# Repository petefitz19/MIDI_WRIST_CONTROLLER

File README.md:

# MIDI_WRIST_CONTROLLER
Code and Schematics for the MIDI wrist controller and its wireless attachments

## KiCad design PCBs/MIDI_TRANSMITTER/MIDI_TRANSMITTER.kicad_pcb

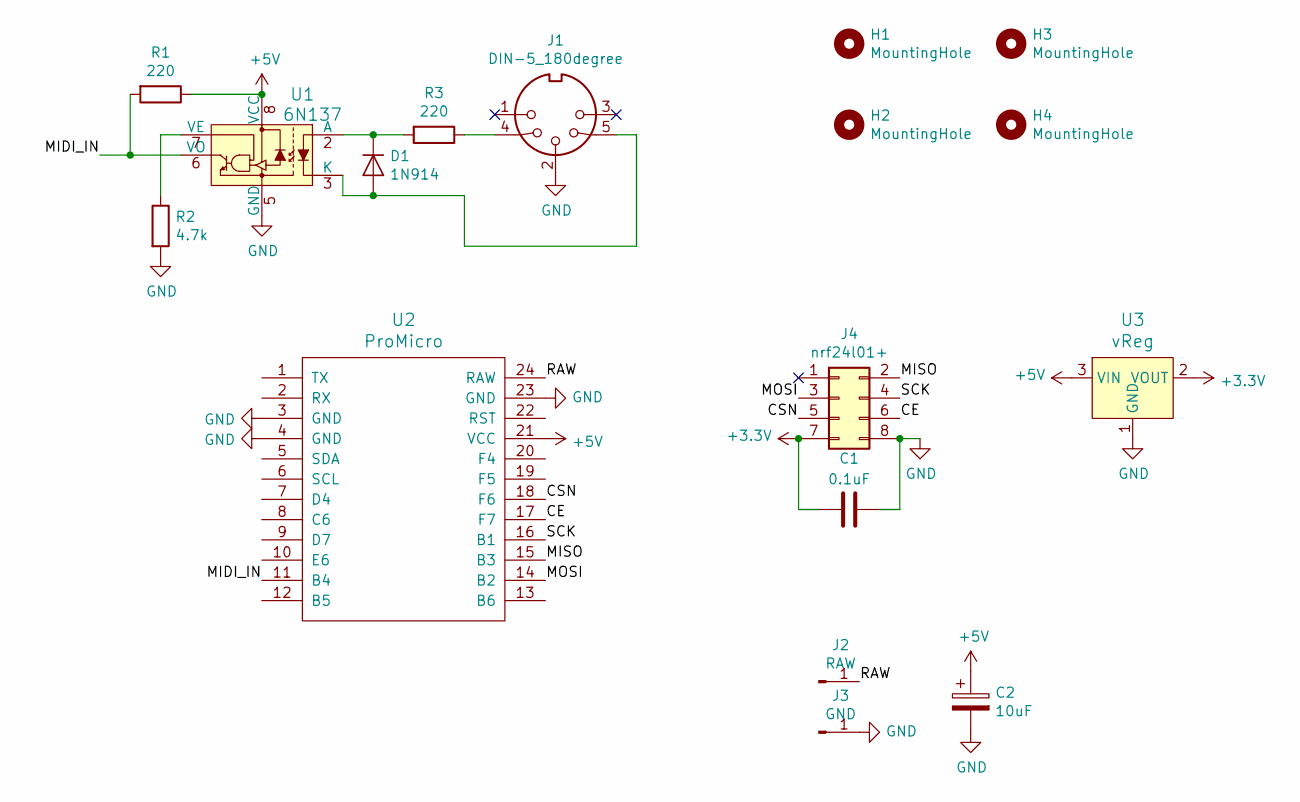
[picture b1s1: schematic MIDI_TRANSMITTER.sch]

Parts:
C1: 0.1uF; C_Disc_D3.0mm_W1.6mm_P2.50mm
C2: 10uF; CP_Radial_D4.0mm_P1.50mm
D1: 1N914; D_DO-34_SOD68_P7.62mm_Horizontal
H1, H2, H3, H4: MountingHole; MountingHole_2.2mm_M2
J1: DIN-5_180degree; Midi_jack
J2: RAW; PinSocket_1x01_P2.54mm_Vertical
J3: GND; PinSocket_1x01_P2.54mm_Vertical
J4: nrf24l01+; PinHeader_2x04_P2.54mm_Vertical
R1, R3: 220; R_Axial_DIN0207_L6.3mm_D2.5mm_P7.62mm_Horizontal
R2: 4.7k; R_Axial_DIN0207_L6.3mm_D2.5mm_P7.62mm_Horizontal
U1: 6N137; DIP-8_W7.62mm; MPN 6N137; Digi-Key_PN 160-1791-ND
U2: ProMicro
U3: vReg; TO-220-3_Vertical; MPN LD1117V33; Digi-Key_PN 497-1491-5-ND

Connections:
+3V3: C1.2, J4.7, U3.2 (VOUT)
+5V: C2.1, R1.1, U1.8 (VCC), U2.21 (VCC), U3.3 (VIN)
/CE: J4.6, U2.17 (F7)
/CSN: J4.5, U2.18 (F6)
/MIDI_IN: R1.2, U1.6 (VO), U2.11 (B4)
/MISO: J4.2, U2.15 (B3)
/MOSI: J4.3, U2.14 (B2)
/RAW: J2.1, U2.24 (RAW)
/SCK: J4.4, U2.16 (B1)
GND: C1.1, C2.2, J1.2, J3.1, J4.8, R2.2, U1.5 (GND), U2.3 (GND), U2.4 (GND), U2.23 (GND), U3.1 (GND)
unnamed: D1.1 (K), R3.2, U1.2 (A)
unnamed: D1.2 (A), J1.5, U1.3 (K)
unnamed: J1.4, R3.1
unnamed: R2.1, U1.7 (VE)

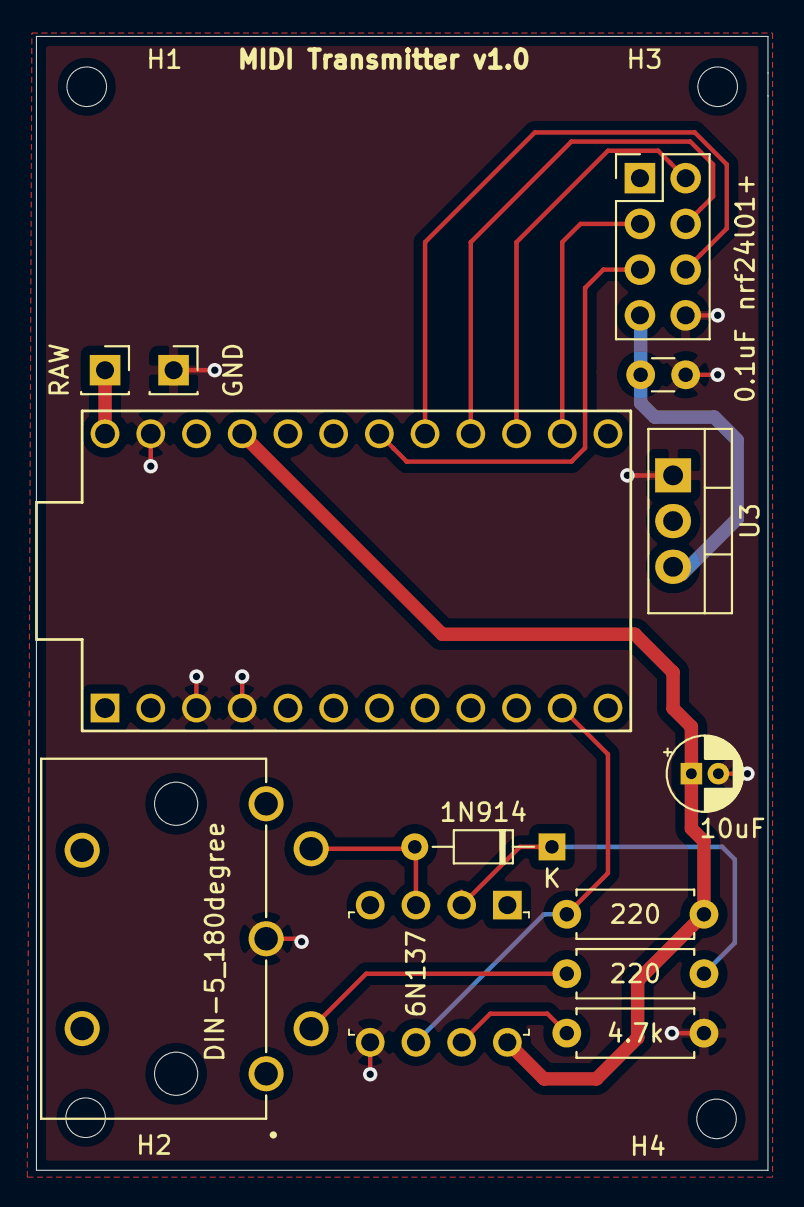
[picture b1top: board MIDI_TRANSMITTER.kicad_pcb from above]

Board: 2 copper layers, 40.6 x 63.0 mm, 17 parts (0 on the bottom side), 14 nets.

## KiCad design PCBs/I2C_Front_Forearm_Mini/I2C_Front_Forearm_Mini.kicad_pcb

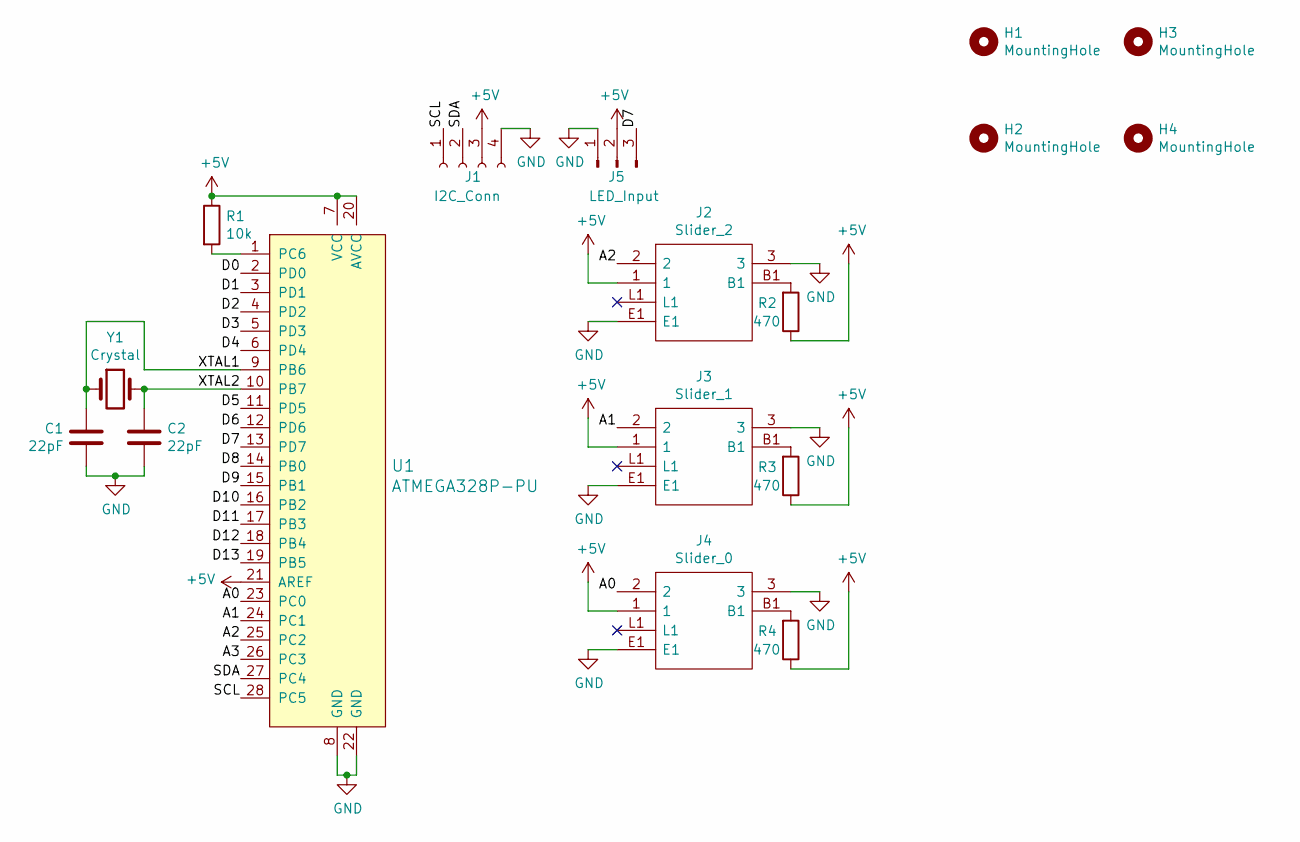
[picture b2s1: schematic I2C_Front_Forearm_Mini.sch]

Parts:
C1, C2: 22pF; C_Disc_D3.0mm_W1.6mm_P2.50mm
H1, H2, H3, H4: MountingHole; MountingHole_2mm
J1: I2C_Conn; JST_PH_B4B-PH-K_1x04_P2.00mm_Vertical
J2: Slider_2; PTL4515O1503B2; Mouser Part Number 652-PTL45-15O1-503B2
J3: Slider_1; PTL4515O1503B2; Mouser Part Number 652-PTL45-15O1-503B2
J4: Slider_0; PTL4515O1503B2; Mouser Part Number 652-PTL45-15O1-503B2
J5: LED_Input; PinHeader_1x03_P2.54mm_Vertical
R1: 10k; R_Axial_DIN0207_L6.3mm_D2.5mm_P7.62mm_Horizontal
R2, R3, R4: 470; R_Axial_DIN0207_L6.3mm_D2.5mm_P7.62mm_Horizontal
U1: ATMEGA328P-PU; DIP-28_W7.62mm; MPN ATMEGA328P-PU; Digi-Key_PN ATMEGA328P-PU-ND
Y1: Crystal; Crystal_HC52-8mm_Vertical

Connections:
+5V: J1.3, J2.1, J3.1, J4.1, J5.2, R1.1, R2.1, R3.1, R4.1, U1.7 (VCC), U1.20 (AVCC), U1.21 (AREF)
/A0: J4.2, U1.23 (PC0)
/A1: J3.2, U1.24 (PC1)
/A2: J2.2, U1.25 (PC2)
/A3: U1.26 (PC3)
/D0: U1.2 (PD0)
/D1: U1.3 (PD1)
/D2: U1.4 (PD2)
/D3: U1.5 (PD3)
/D4: U1.6 (PD4)
/D5: U1.11 (PD5)
/D6: U1.12 (PD6)
/D7: J5.3, U1.13 (PD7)
/D8: U1.14 (PB0)
/D9: U1.15 (PB1)
/D10: U1.16 (PB2)
/D11: U1.17 (PB3)
/D12: U1.18 (PB4)
/D13: U1.19 (PB5)
/SCL: J1.1, U1.28 (PC5)
/SDA: J1.2, U1.27 (PC4)
/XTAL1: C1.2, U1.9 (PB6), Y1.1
/XTAL2: C2.1, U1.10 (PB7), Y1.2
GND: C1.1, C2.2, J1.4, J2.3, J2.E1, J3.3, J3.E1, J4.3, J4.E1, J5.1, U1.8 (GND), U1.22 (GND)
unnamed: J2.B1, R2.2
unnamed: J3.B1, R3.2
unnamed: J4.B1, R4.2
unnamed: R1.2, U1.1 (PC6)

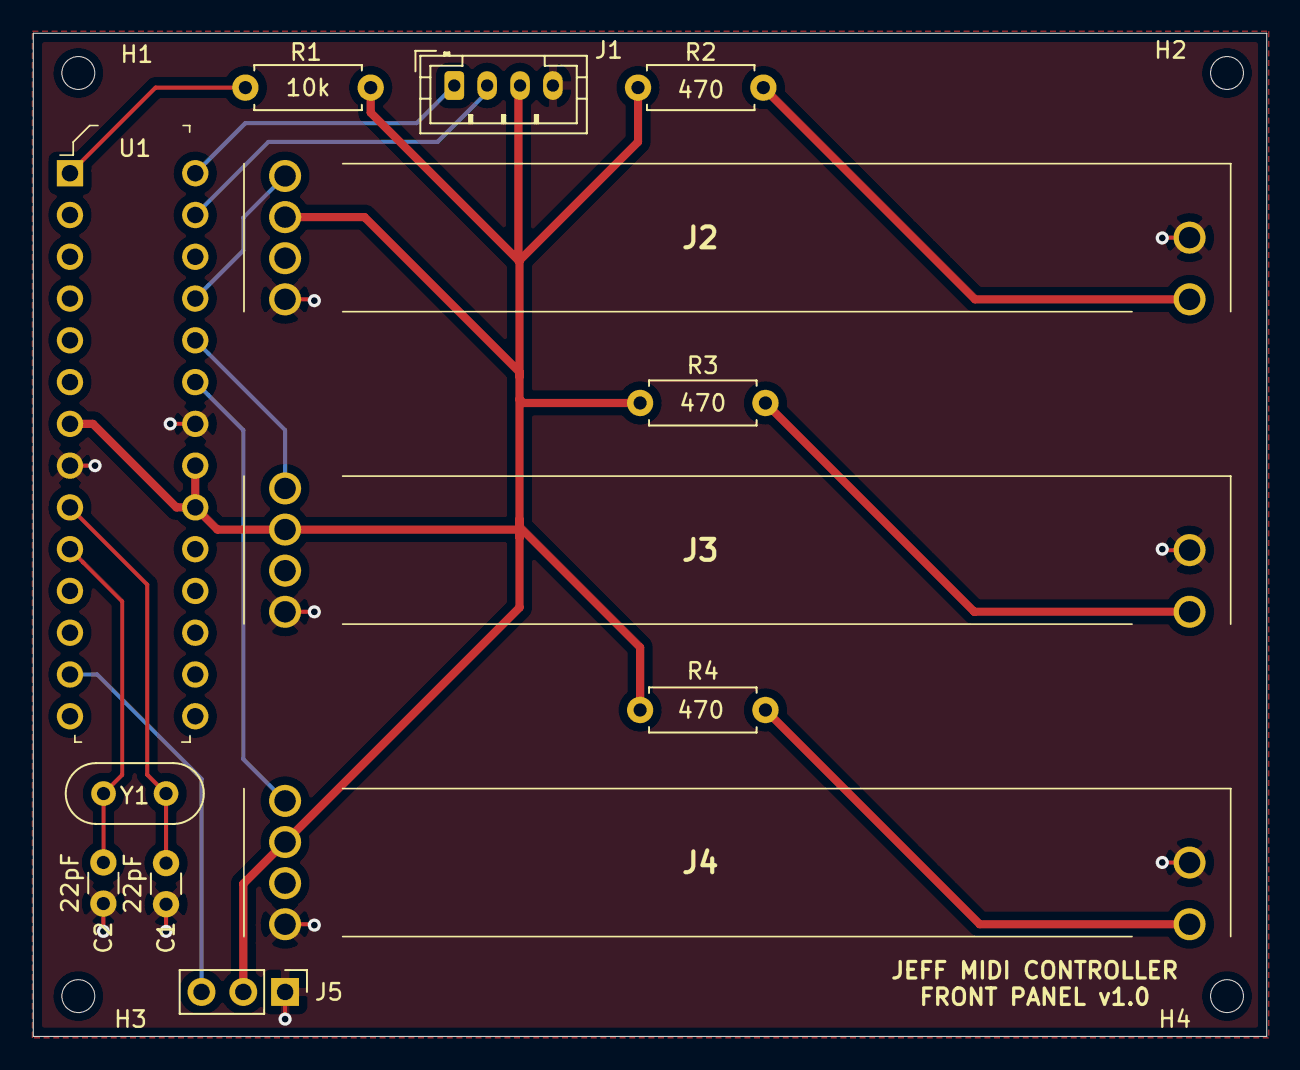
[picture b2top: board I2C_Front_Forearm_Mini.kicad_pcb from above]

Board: 2 copper layers, 75.0 x 61.0 mm, 17 parts (0 on the bottom side), 14 nets.

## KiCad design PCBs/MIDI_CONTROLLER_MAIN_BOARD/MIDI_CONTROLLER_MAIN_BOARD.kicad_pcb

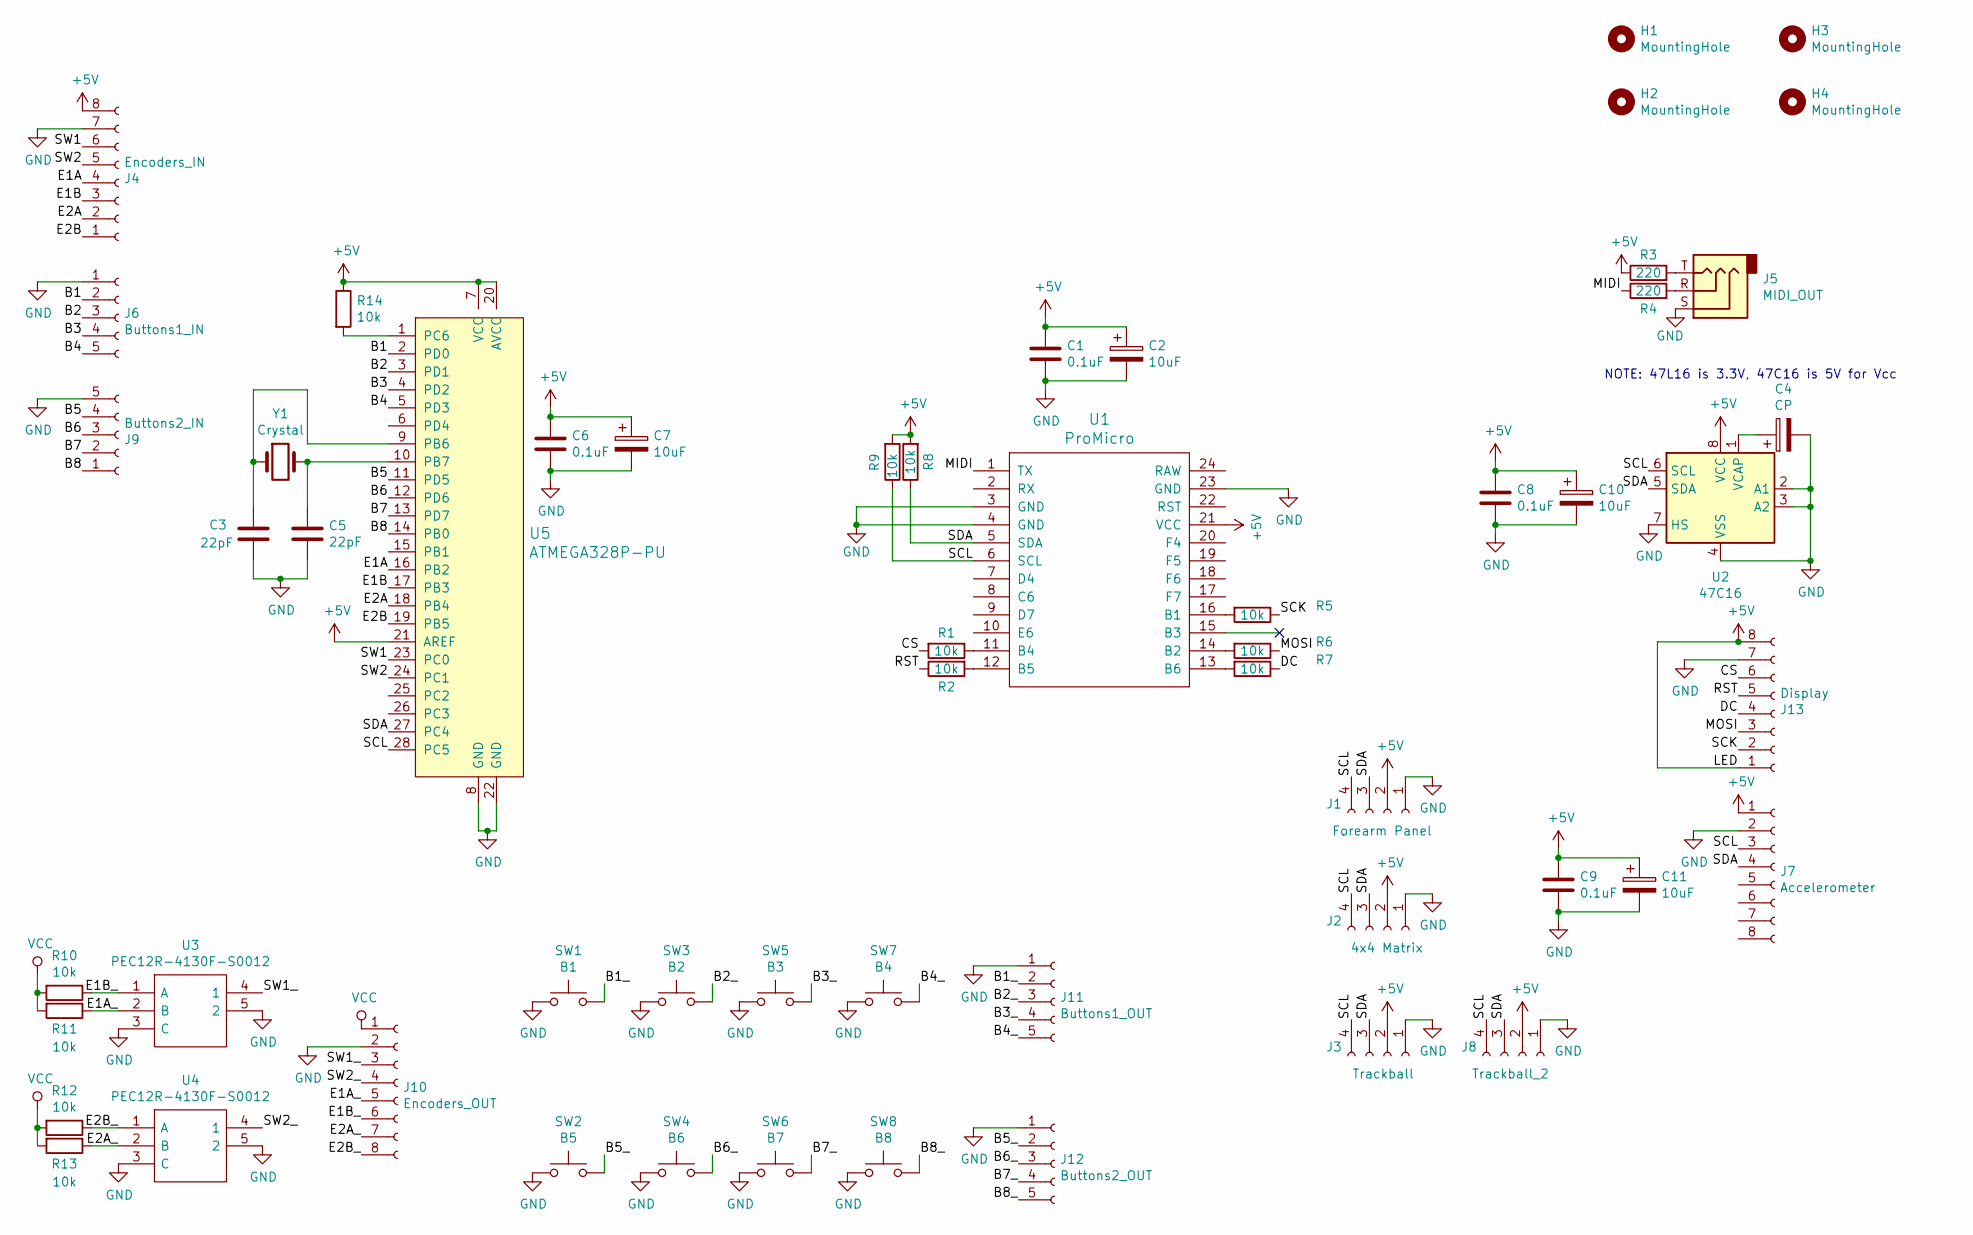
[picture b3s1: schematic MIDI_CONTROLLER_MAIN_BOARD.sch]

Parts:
C1, C6, C8, C9: 0.1uF; C_Disc_D3.0mm_W1.6mm_P2.50mm
C2, C7, C10, C11: 10uF; CP_Radial_D4.0mm_P1.50mm
C3, C5: 22pF; C_Disc_D3.0mm_W1.6mm_P2.50mm
C4: CP; CP_Radial_D4.0mm_P1.50mm
H1, H2, H3, H4: MountingHole; MountingHole_2mm
J1: Forearm Panel; JST_PH_B4B-PH-K_1x04_P2.00mm_Vertical
J2: 4x4 Matrix; JST_PH_B4B-PH-K_1x04_P2.00mm_Vertical
J3: Trackball; JST_PH_B4B-PH-K_1x04_P2.00mm_Vertical
J4: Encoders_IN; JST_XH_B8B-XH-AM_1x08_P2.50mm_Vertical
J5: MIDI_OUT; Jack_3.5mm_Ledino_KB3SPRS_Horizontal
J6: Buttons1_IN; JST_XH_B5B-XH-AM_1x05_P2.50mm_Vertical
J7: Accelerometer; PinHeader_1x08_P2.54mm_Vertical
J8: Trackball_2; JST_PH_B4B-PH-K_1x04_P2.00mm_Vertical
J9: Buttons2_IN; JST_XH_B5B-XH-AM_1x05_P2.50mm_Vertical
J10: Encoders_OUT; PinHeader_1x08_P2.54mm_Vertical
J11: Buttons1_OUT; PinSocket_1x05_P2.54mm_Vertical
J12: Buttons2_OUT; PinSocket_1x05_P2.54mm_Vertical
J13: Display; PinSocket_1x08_P2.54mm_Horizontal
R1, R2, R5, R6, R7, R8, R9, R10, R11, R12, R13, R14: 10k; R_Axial_DIN0207_L6.3mm_D2.5mm_P7.62mm_Horizontal
R3, R4: 220; R_Axial_DIN0207_L6.3mm_D2.5mm_P7.62mm_Horizontal
SW1: B1; SW_PUSH_6mm_H5mm
SW2: B5; SW_PUSH_6mm_H5mm
SW3: B2; SW_PUSH_6mm_H5mm
SW4: B6; SW_PUSH_6mm_H5mm
SW5: B3; SW_PUSH_6mm_H5mm
SW6: B7; SW_PUSH_6mm_H5mm
SW7: B4; SW_PUSH_6mm_H5mm
SW8: B8; SW_PUSH_6mm_H5mm
U1: ProMicro
U2: 47C16; DIP-8_W7.62mm
U3, U4: PEC12R-4130F-S0012; PEC12R-4XXXF-SXXXX_1; Mouser Part Number 652-PEC12R-4130F-S12
U5: ATMEGA328P-PU; DIP-28_W7.62mm; MPN ATMEGA328P-PU; Digi-Key_PN ATMEGA328P-PU-ND
Y1: Crystal; Crystal_HC18-U_Vertical

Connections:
+5V: C1.1, C2.1, C6.1, C7.1, C8.1, C9.1, C10.1, C11.1, J1.2, J2.2, J3.2, J4.8, J7.1, J8.2, J13.1, J13.8, R3.1, R8.2, R9.2, R14.1, U1.21 (VCC), U2.8 (VCC), U5.7 (VCC), U5.20 (AVCC), U5.21 (AREF)
/B1: J6.2, U5.2 (PD0)
/B1_: J11.2, SW1.2
/B2: J6.3, U5.3 (PD1)
/B2_: J11.3, SW3.2
/B3: J6.4, U5.4 (PD2)
/B3_: J11.4, SW5.2
/B4: J6.5, U5.5 (PD3)
/B4_: J11.5, SW7.2
/B5: J9.4, U5.11 (PD5)
/B5_: J12.2, SW2.2
/B6: J9.3, U5.12 (PD6)
/B6_: J12.3, SW4.2
/B7: J9.2, U5.13 (PD7)
/B7_: J12.4, SW6.2
/B8: J9.1, U5.14 (PB0)
/B8_: J12.5, SW8.2
/CS: J13.6, R1.2
/DC: J13.4, R7.1
/E1A: J4.4, U5.16 (PB2)
/E1A_: J10.5, R11.1, U3.2 (B)
/E1B: J4.3, U5.17 (PB3)
/E1B_: J10.6, R10.1, U3.1 (A)
/E2A: J4.2, U5.18 (PB4)
/E2A_: J10.7, R13.1, U4.2 (B)
/E2B: J4.1, U5.19 (PB5)
/E2B_: J10.8, R12.1, U4.1 (A)
/MIDI: R4.1, U1.1 (TX)
/MOSI: J13.3, R6.1
/RST: J13.5, R2.1
/SCK: J13.2, R5.1
/SCL: J1.4, J2.4, J3.4, J7.3, J8.4, R9.1, U1.6 (SCL), U2.6 (SCL), U5.28 (PC5)
/SDA: J1.3, J2.3, J3.3, J7.4, J8.3, R8.1, U1.5 (SDA), U2.5 (SDA), U5.27 (PC4)
/SW1: J4.6, U5.23 (PC0)
/SW1_: J10.3, U3.4 (1)
/SW2: J4.5, U5.24 (PC1)
/SW2_: J10.4, U4.4 (1)
GND: C1.2, C2.2, C3.2, C4.2, C5.2, C6.2, C7.2, C8.2, C9.2, C10.2, C11.2, J1.1, J2.1, J3.1, J4.7, J5.S, J6.1, J7.2, J8.1, J9.5, J10.2, J11.1, J12.1, J13.7, SW1.1, SW2.1, SW3.1, SW4.1, SW5.1, SW6.1, SW7.1, SW8.1, U1.3 (GND), U1.4 (GND), U1.23 (GND), U2.2 (A1), U2.3 (A2), U2.4 (VSS), U2.7 (HS), U3.3 (C), U3.5 (2), U4.3 (C), U4.5 (2), U5.8 (GND), U5.22 (GND)
unnamed: C3.1, U5.9 (PB6), Y1.1
unnamed: C4.1, U2.1 (VCAP)
unnamed: C5.1, U5.10 (PB7), Y1.2
unnamed: J5.R, R4.2
unnamed: J5.T, R3.2
unnamed: R1.1, U1.11 (B4)
unnamed: R2.2, U1.12 (B5)
unnamed: R5.2, U1.16 (B1)
unnamed: R6.2, U1.14 (B2)
unnamed: R7.2, U1.13 (B6)
unnamed: R14.2, U5.1 (PC6)
VCC: J10.1, R10.2, R11.2, R12.2, R13.2

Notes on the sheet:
NOTE: 47L16 is 3.3V, 47C16 is 5V for Vcc

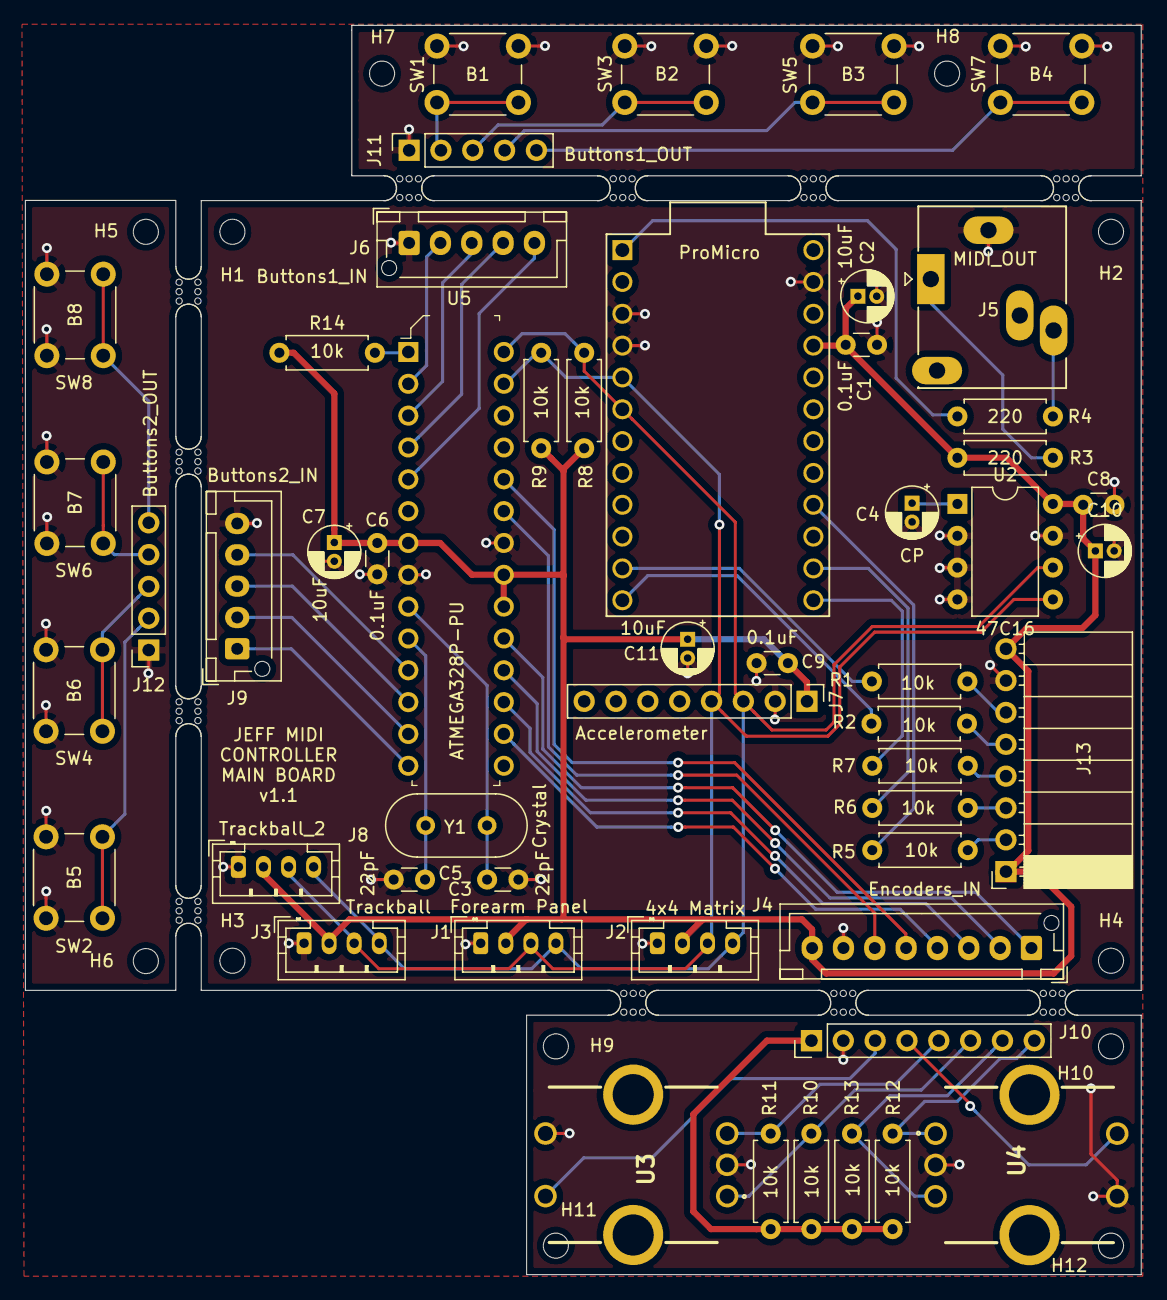
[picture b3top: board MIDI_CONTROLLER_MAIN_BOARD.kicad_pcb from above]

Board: 2 copper layers, 89.0 x 99.7 mm, 75 parts (0 on the bottom side), 50 nets.

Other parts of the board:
H5, H6, H7, H8, H9, H10, H11, H12: MountingHole_2mm
mouse-bite-2mm-slot, mouse-bite-2mm-slot#2, mouse-bite-2mm-slot#3, mouse-bite-2mm-slot#4, mouse-bite-2mm-slot#5, mouse-bite-2mm-slot#6, mouse-bite-2mm-slot#7, mouse-bite-2mm-slot#8, mouse-bite-2mm-slot#9, mouse-bite-2mm-slot#10, mouse-bite-2mm-slot#11: VAL**; mouse-bite-2mm-slot

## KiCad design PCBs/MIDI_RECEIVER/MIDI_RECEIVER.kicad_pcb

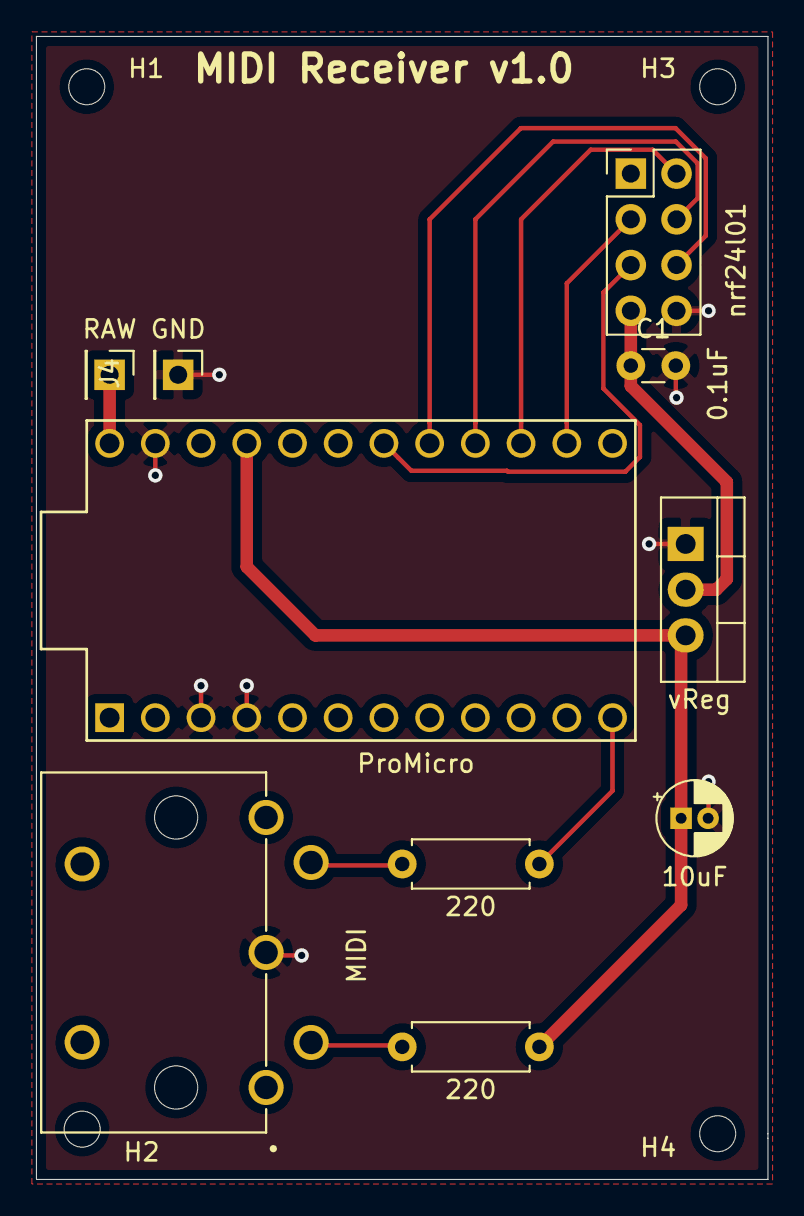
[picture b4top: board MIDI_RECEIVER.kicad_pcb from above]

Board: 2 copper layers, 40.6 x 63.5 mm, 14 parts (0 on the bottom side), 12 nets.

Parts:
C1: 0.1uF; C_Disc_D3.0mm_W1.6mm_P2.50mm
C2: 10uF; CP_Radial_D4.0mm_P1.50mm
H1, H2, H3, H4: MountingHole; MountingHole_2mm
J1: MIDI; Midi_jack
J2: nrf24l01; PinHeader_2x04_P2.54mm_Vertical
J3: RAW; PinHeader_1x01_P2.54mm_Vertical
J4: GND; PinHeader_1x01_P2.54mm_Vertical
R1, R2: 220; R_Axial_DIN0207_L6.3mm_D2.5mm_P7.62mm_Horizontal
U1: ProMicro
U2: vReg; TO-220-3_Vertical

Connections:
+3V3: C1.1, J2.7, U2.2
+5V: C2.1, R2.2, U1.21, U2.3
/CE: J2.6, U1.17
/CSN: J2.5, U1.18
/MIDI_IN: R1.2, U1.12
/MISO: J2.2, U1.15
/MOSI: J2.3, U1.14
/RAW: J3.1, U1.24
/SCK: J2.4, U1.16
GND: C1.2, C2.2, J1.2, J2.8, J4.1, U1.3, U1.4, U1.23, U2.1
unnamed: J1.4, R2.1
unnamed: J1.5, R1.1

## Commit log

2020-08-13 Added project files
